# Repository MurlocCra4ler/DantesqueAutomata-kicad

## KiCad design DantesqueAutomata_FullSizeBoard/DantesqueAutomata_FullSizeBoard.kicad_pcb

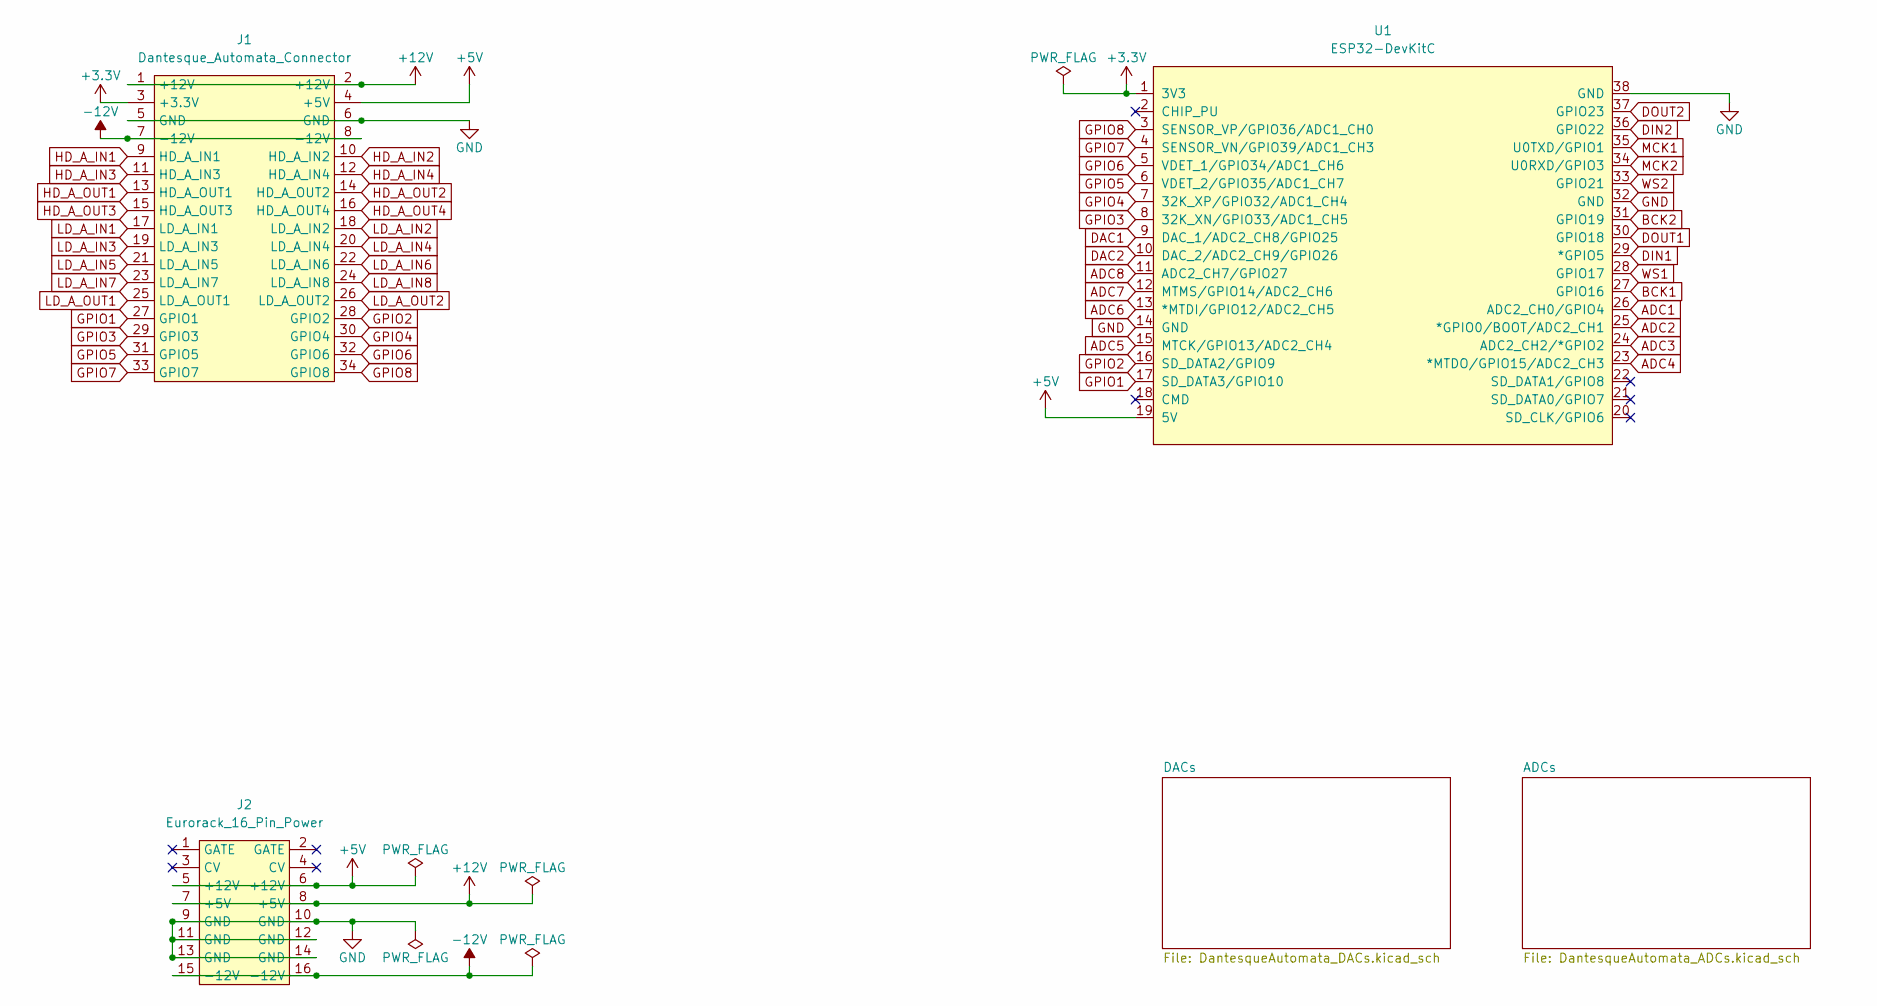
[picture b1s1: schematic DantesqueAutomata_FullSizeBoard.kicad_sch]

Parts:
J1: Dantesque_Automata_Connector
J2: Eurorack_16_Pin_Power
U1: ESP32-DevKitC

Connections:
+3.3V: J1.3 (+3.3V), U1.1 (3V3); also elsewhere on the board
+5V: J1.4 (+5V), J2.5 (+12V), J2.6 (+12V), U1.19 (5V); also elsewhere on the board
+12V: J1.1 (+12V), J1.2 (+12V), J2.7 (+5V), J2.8 (+5V); also elsewhere on the board
-12V: J1.7 (-12V), J1.8 (-12V), J2.15 (-12V), J2.16 (-12V); also elsewhere on the board
ADC1: U1.26 (ADC2_CH0/GPIO4); also elsewhere on the board
ADC2: U1.25 (*GPIO0/BOOT/ADC2_CH1); also elsewhere on the board
ADC3: U1.24 (ADC2_CH2/*GPIO2); also elsewhere on the board
ADC4: U1.23 (*MTDO/GPIO15/ADC2_CH3); also elsewhere on the board
ADC5: U1.15 (MTCK/GPIO13/ADC2_CH4); also elsewhere on the board
ADC6: U1.13 (*MTDI/GPIO12/ADC2_CH5); also elsewhere on the board
ADC7: U1.12 (MTMS/GPIO14/ADC2_CH6); also elsewhere on the board
ADC8: U1.11 (ADC2_CH7/GPIO27); also elsewhere on the board
BCK1: U1.27 (GPIO16); also elsewhere on the board
BCK2: U1.31 (GPIO19); also elsewhere on the board
DAC1: U1.9 (DAC_1/ADC2_CH8/GPIO25); also elsewhere on the board
DAC2: U1.10 (DAC_2/ADC2_CH9/GPIO26); also elsewhere on the board
DIN1: U1.29 (*GPIO5); also elsewhere on the board
DIN2: U1.36 (GPIO22); also elsewhere on the board
DOUT1: U1.30 (GPIO18); also elsewhere on the board
DOUT2: U1.37 (GPIO23); also elsewhere on the board
GND: J1.5 (GND), J1.6 (GND), J2.9 (GND), J2.10 (GND), J2.11 (GND), J2.12 (GND), J2.13 (GND), J2.14 (GND), U1.14 (GND), U1.32 (GND), U1.38 (GND); also elsewhere on the board
GPIO1: J1.27 (GPIO1), U1.17 (SD_DATA3/GPIO10)
GPIO2: J1.28 (GPIO2), U1.16 (SD_DATA2/GPIO9)
GPIO3: J1.29 (GPIO3), U1.8 (32K_XN/GPIO33/ADC1_CH5)
GPIO4: J1.30 (GPIO4), U1.7 (32K_XP/GPIO32/ADC1_CH4)
GPIO5: J1.31 (GPIO5), U1.6 (VDET_2/GPIO35/ADC1_CH7)
GPIO6: J1.32 (GPIO6), U1.5 (VDET_1/GPIO34/ADC1_CH6)
GPIO7: J1.33 (GPIO7), U1.4 (SENSOR_VN/GPIO39/ADC1_CH3)
GPIO8: J1.34 (GPIO8), U1.3 (SENSOR_VP/GPIO36/ADC1_CH0)
HD_A_IN1: J1.9 (HD_A_IN1); also elsewhere on the board
HD_A_IN2: J1.10 (HD_A_IN2); also elsewhere on the board
HD_A_IN3: J1.11 (HD_A_IN3); also elsewhere on the board
HD_A_IN4: J1.12 (HD_A_IN4); also elsewhere on the board
HD_A_OUT1: J1.13 (HD_A_OUT1); also elsewhere on the board
HD_A_OUT2: J1.14 (HD_A_OUT2); also elsewhere on the board
HD_A_OUT3: J1.15 (HD_A_OUT3); also elsewhere on the board
HD_A_OUT4: J1.16 (HD_A_OUT4); also elsewhere on the board
LD_A_IN1: J1.17 (LD_A_IN1); also elsewhere on the board
LD_A_IN2: J1.18 (LD_A_IN2); also elsewhere on the board
LD_A_IN3: J1.19 (LD_A_IN3); also elsewhere on the board
LD_A_IN4: J1.20 (LD_A_IN4); also elsewhere on the board
LD_A_IN5: J1.21 (LD_A_IN5); also elsewhere on the board
LD_A_IN6: J1.22 (LD_A_IN6); also elsewhere on the board
LD_A_IN7: J1.23 (LD_A_IN7); also elsewhere on the board
LD_A_IN8: J1.24 (LD_A_IN8); also elsewhere on the board
LD_A_OUT1: J1.25 (LD_A_OUT1); also elsewhere on the board
LD_A_OUT2: J1.26 (LD_A_OUT2); also elsewhere on the board
MCK1: U1.35 (U0TXD/GPIO1); also elsewhere on the board
MCK2: U1.34 (U0RXD/GPIO3); also elsewhere on the board
WS1: U1.28 (GPIO17); also elsewhere on the board
WS2: U1.33 (GPIO21); also elsewhere on the board

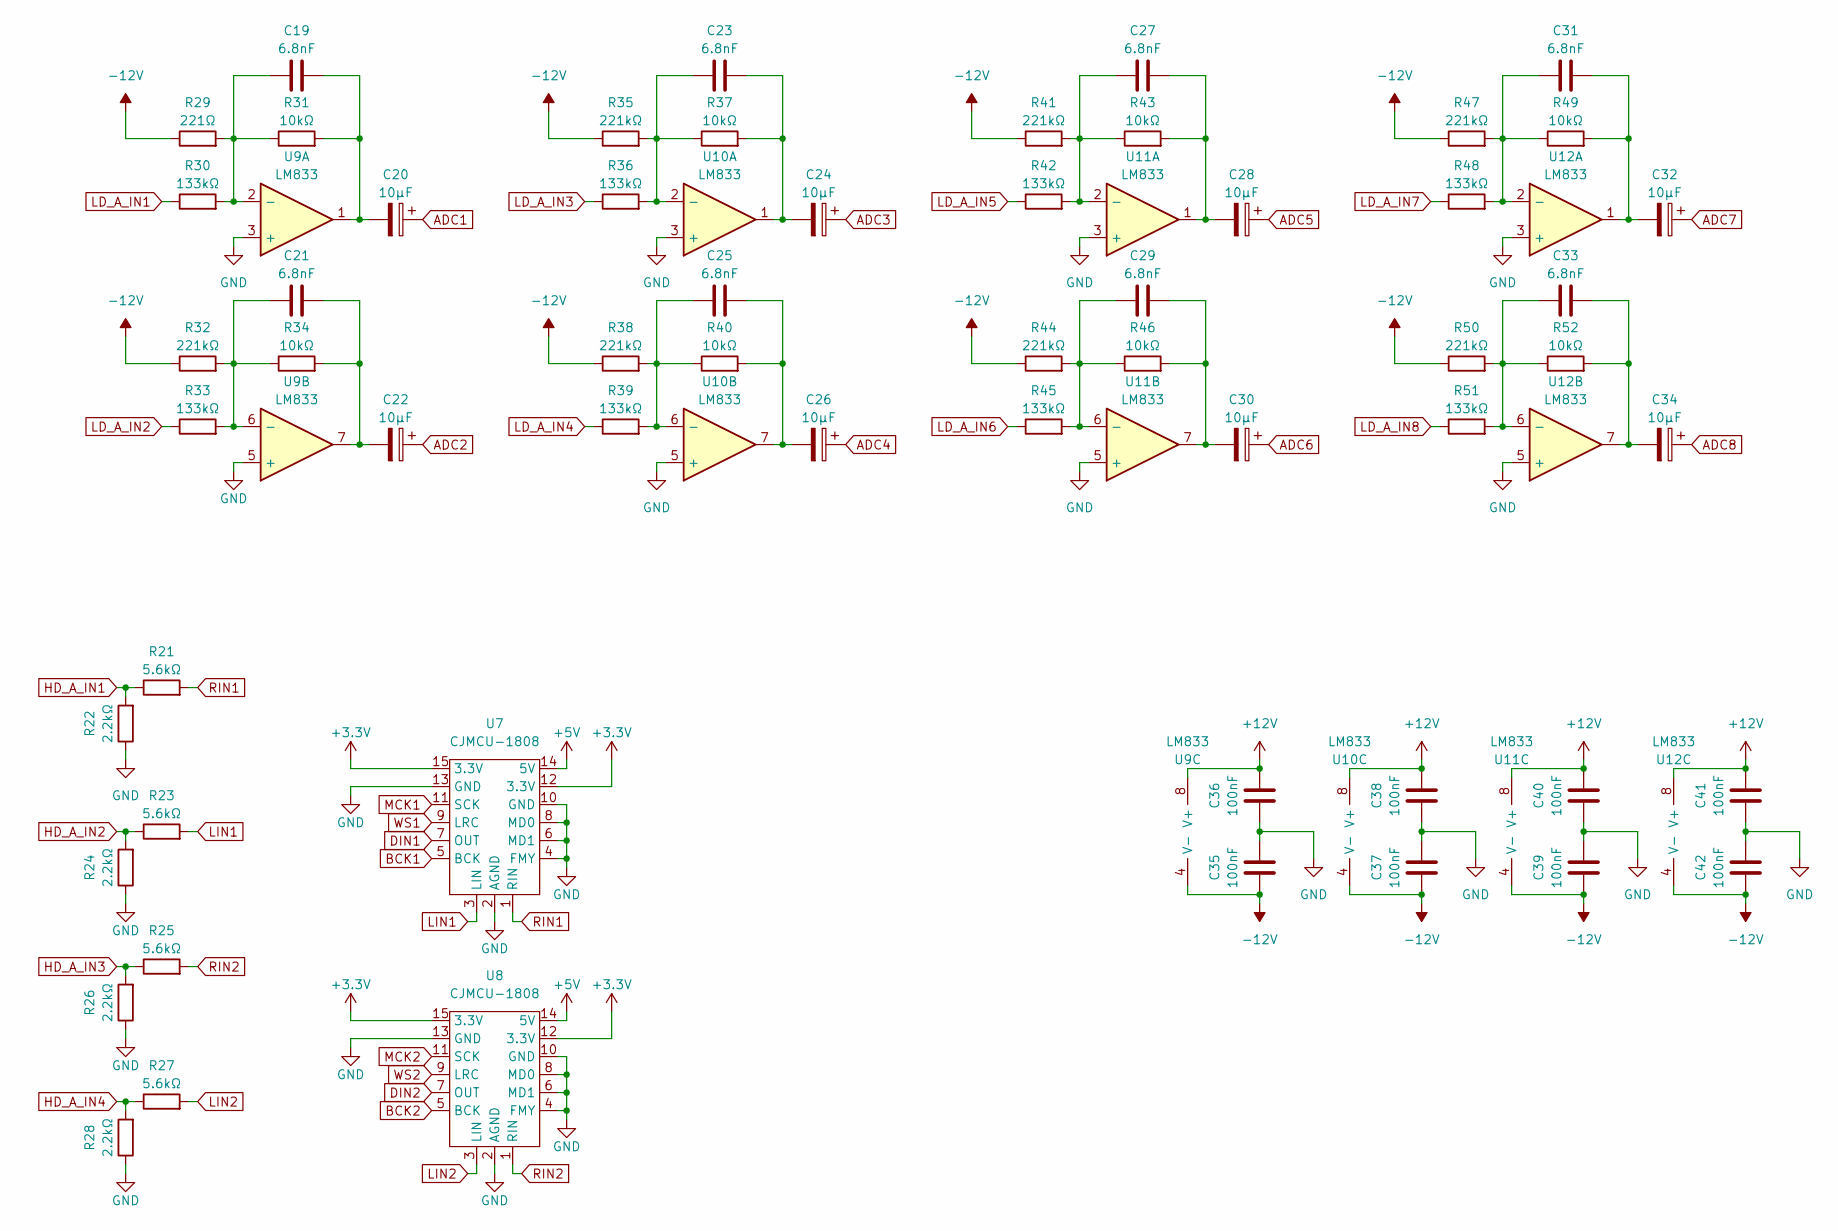
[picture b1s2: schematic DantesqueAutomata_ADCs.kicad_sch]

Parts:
C19, C21, C23, C25, C27, C29, C31, C33: 6.8nF; C_Disc_D4.3mm_W1.9mm_P5.00mm
C20, C22, C24, C26, C28, C30, C32, C34: 10µF; CP_Radial_D5.0mm_P2.00mm
C35, C36, C37, C38, C39, C40, C41, C42: 100nF; C_Disc_D4.3mm_W1.9mm_P5.00mm
R21, R23, R25, R27: 5.6kΩ; R_Axial_DIN0207_L6.3mm_D2.5mm_P10.16mm_Horizontal
R22, R24, R26, R28: 2.2kΩ; R_Axial_DIN0207_L6.3mm_D2.5mm_P10.16mm_Horizontal
R29: 221Ω; R_Axial_DIN0207_L6.3mm_D2.5mm_P10.16mm_Horizontal
R30, R33, R36, R39, R42, R45, R48, R51: 133kΩ; R_Axial_DIN0207_L6.3mm_D2.5mm_P10.16mm_Horizontal
R31, R34, R37, R40, R43, R46, R49, R52: 10kΩ; R_Axial_DIN0207_L6.3mm_D2.5mm_P10.16mm_Horizontal
R32, R35, R38, R41, R44, R47, R50: 221kΩ; R_Axial_DIN0207_L6.3mm_D2.5mm_P10.16mm_Horizontal
U7, U8: CJMCU-1808
U9, U10, U11, U12: LM833; DIP-8_W7.62mm

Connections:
+3.3V: U7.12 (3.3V), U7.15 (3.3V), U8.12 (3.3V), U8.15 (3.3V); also elsewhere on the board
+5V: U7.14 (5V), U8.14 (5V); also elsewhere on the board
+12V: C36.2, C38.2, C40.2, C41.2, U9.8 (V+), U10.8 (V+), U11.8 (V+), U12.8 (V+); also elsewhere on the board
-12V: C35.1, C37.1, C39.1, C42.1, R29.1, R32.1, R35.1, R38.1, R41.1, R44.1, R47.1, R50.1, U9.4 (V-), U10.4 (V-), U11.4 (V-), U12.4 (V-); also elsewhere on the board
ADC1: C20.1; also elsewhere on the board
ADC2: C22.1; also elsewhere on the board
ADC3: C24.1; also elsewhere on the board
ADC4: C26.1; also elsewhere on the board
ADC5: C28.1; also elsewhere on the board
ADC6: C30.1; also elsewhere on the board
ADC7: C32.1; also elsewhere on the board
ADC8: C34.1; also elsewhere on the board
BCK1: U7.5 (BCK); also elsewhere on the board
BCK2: U8.5 (BCK); also elsewhere on the board
DIN1: U7.7 (OUT); also elsewhere on the board
DIN2: U8.7 (OUT); also elsewhere on the board
GND: C35.2, C36.1, C37.2, C38.1, C39.2, C40.1, C41.1, C42.2, R22.1, R24.1, R26.1, R28.1, U7.2 (AGND), U7.4 (FMY), U7.6 (MD1), U7.8 (MD0), U7.10 (GND), U7.13 (GND), U8.2 (AGND), U8.4 (FMY), U8.6 (MD1), U8.8 (MD0), U8.10 (GND), U8.13 (GND), U9.3 (+), U9.5 (+), U10.3 (+), U10.5 (+), U11.3 (+), U11.5 (+), U12.3 (+), U12.5 (+); also elsewhere on the board
HD_A_IN1: R21.1, R22.2; also elsewhere on the board
HD_A_IN2: R23.1, R24.2; also elsewhere on the board
HD_A_IN3: R25.1, R26.2; also elsewhere on the board
HD_A_IN4: R27.1, R28.2; also elsewhere on the board
LD_A_IN1: R30.1; also elsewhere on the board
LD_A_IN2: R33.1; also elsewhere on the board
LD_A_IN3: R36.1; also elsewhere on the board
LD_A_IN4: R39.1; also elsewhere on the board
LD_A_IN5: R42.1; also elsewhere on the board
LD_A_IN6: R45.1; also elsewhere on the board
LD_A_IN7: R48.1; also elsewhere on the board
LD_A_IN8: R51.1; also elsewhere on the board
LIN1: R23.2, U7.3 (LIN)
LIN2: R27.2, U8.3 (LIN)
MCK1: U7.11 (SCK); also elsewhere on the board
MCK2: U8.11 (SCK); also elsewhere on the board
unnamed: C19.1, R29.2, R30.2, R31.1, U9.2 (-)
unnamed: C19.2, C20.2, R31.2, U9.1
unnamed: C21.1, R32.2, R33.2, R34.1, U9.6 (-)
unnamed: C21.2, C22.2, R34.2, U9.7
unnamed: C23.1, R35.2, R36.2, R37.1, U10.2 (-)
unnamed: C23.2, C24.2, R37.2, U10.1
unnamed: C25.1, R38.2, R39.2, R40.1, U10.6 (-)
unnamed: C25.2, C26.2, R40.2, U10.7
unnamed: C27.1, R41.2, R42.2, R43.1, U11.2 (-)
unnamed: C27.2, C28.2, R43.2, U11.1
unnamed: C29.1, R44.2, R45.2, R46.1, U11.6 (-)
unnamed: C29.2, C30.2, R46.2, U11.7
unnamed: C31.1, R47.2, R48.2, R49.1, U12.2 (-)
unnamed: C31.2, C32.2, R49.2, U12.1
unnamed: C33.1, R50.2, R51.2, R52.1, U12.6 (-)
unnamed: C33.2, C34.2, R52.2, U12.7
RIN1: R21.2, U7.1 (RIN)
RIN2: R25.2, U8.1 (RIN)
WS1: U7.9 (LRC); also elsewhere on the board
WS2: U8.9 (LRC); also elsewhere on the board

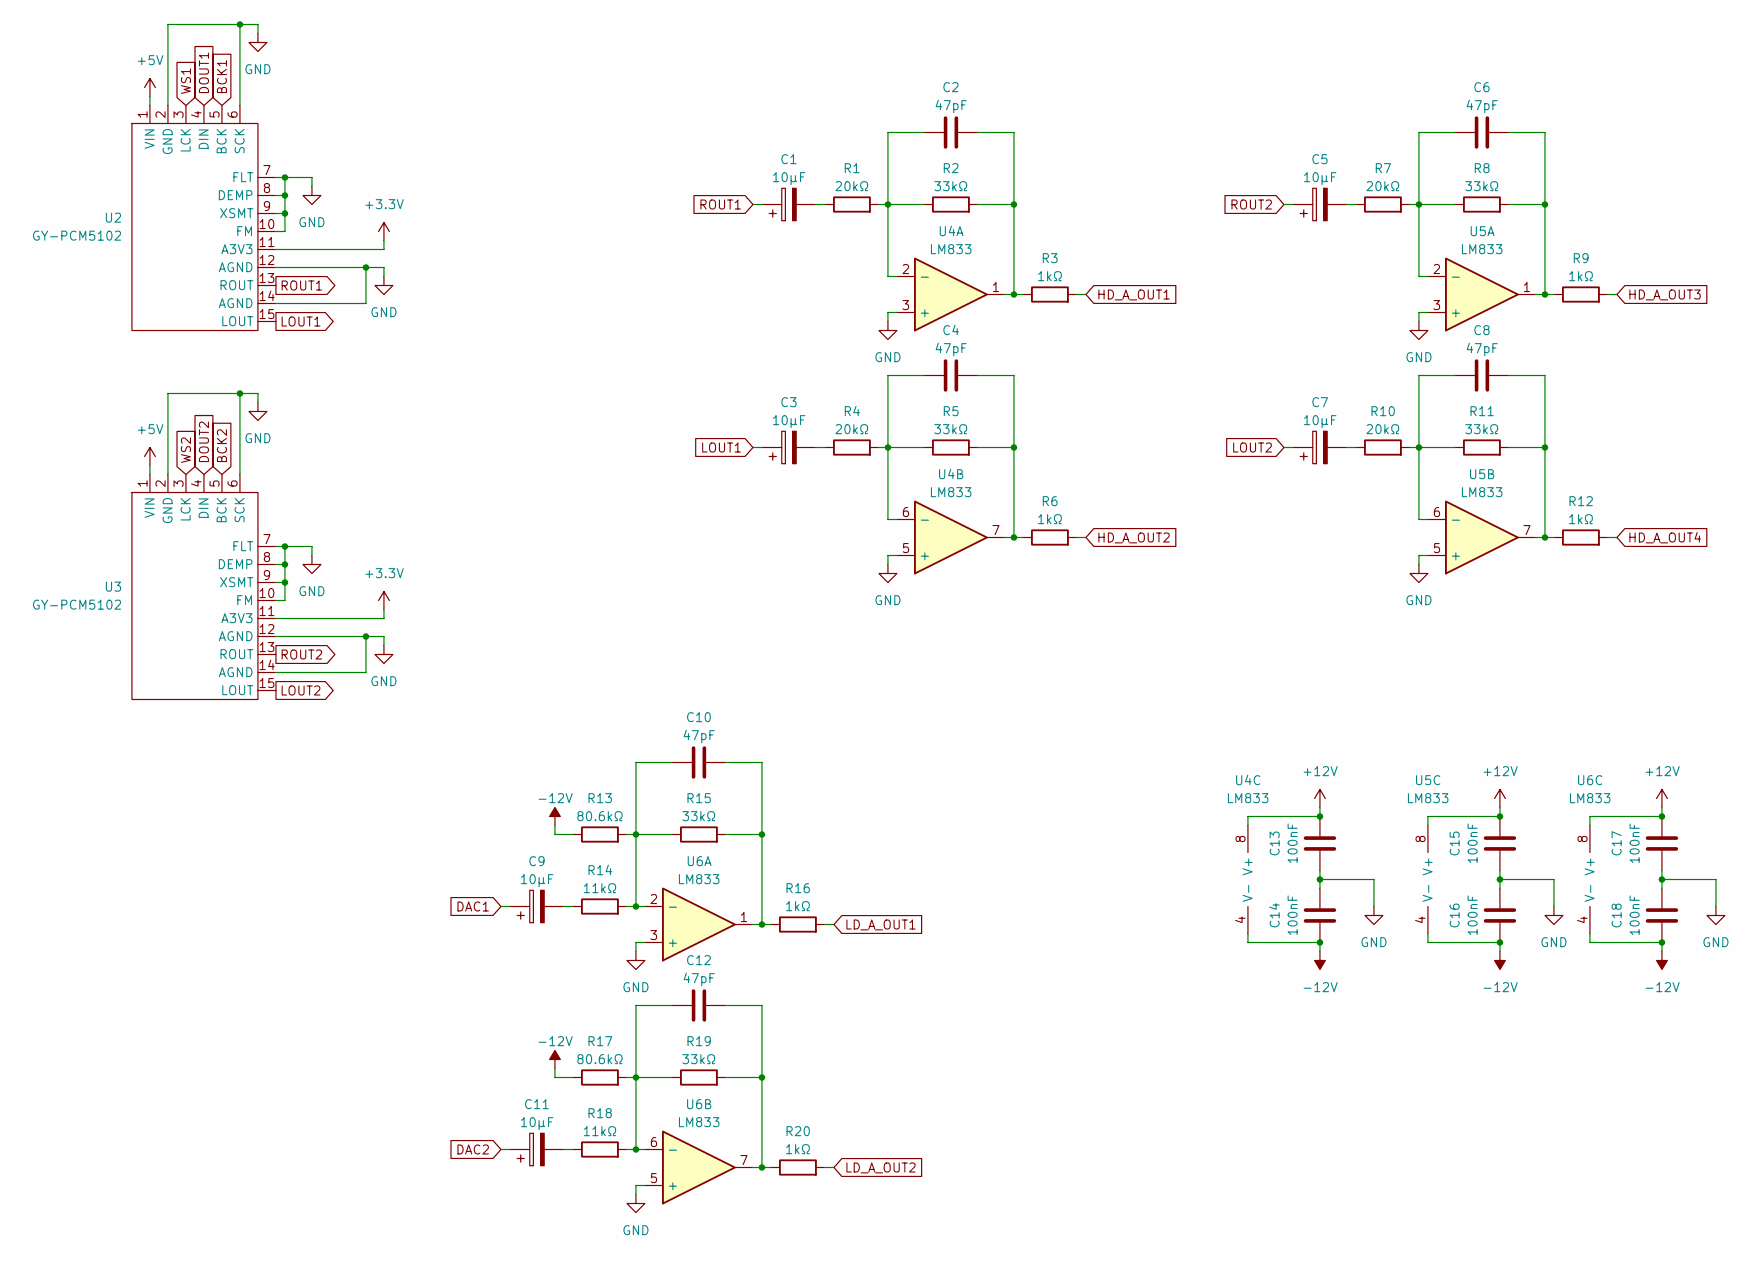
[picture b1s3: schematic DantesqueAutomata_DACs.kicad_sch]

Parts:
C1, C3, C5, C7, C9, C11: 10µF; CP_Radial_D5.0mm_P2.00mm
C2, C4, C6, C8, C10, C12: 47pF; C_Disc_D4.3mm_W1.9mm_P5.00mm
C13, C14, C15, C16, C17, C18: 100nF; C_Disc_D4.3mm_W1.9mm_P5.00mm
R1, R4, R7, R10: 20kΩ; R_Axial_DIN0207_L6.3mm_D2.5mm_P10.16mm_Horizontal
R2, R5, R8, R11, R15, R19: 33kΩ; R_Axial_DIN0207_L6.3mm_D2.5mm_P10.16mm_Horizontal
R3, R6, R9, R12, R16, R20: 1kΩ; R_Axial_DIN0207_L6.3mm_D2.5mm_P10.16mm_Horizontal
R13, R17: 80.6kΩ; R_Axial_DIN0207_L6.3mm_D2.5mm_P10.16mm_Horizontal
R14, R18: 11kΩ; R_Axial_DIN0207_L6.3mm_D2.5mm_P10.16mm_Horizontal
U2, U3: GY-PCM5102
U4, U5, U6: LM833; DIP-8_W7.62mm

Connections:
+3.3V: U2.11 (A3V3), U3.11 (A3V3); also elsewhere on the board
+5V: U2.1 (VIN), U3.1 (VIN); also elsewhere on the board
+12V: C13.2, C15.2, C17.2, U4.8 (V+), U5.8 (V+), U6.8 (V+); also elsewhere on the board
-12V: C14.1, C16.1, C18.1, R13.1, R17.1, U4.4 (V-), U5.4 (V-), U6.4 (V-); also elsewhere on the board
BCK1: U2.5 (BCK); also elsewhere on the board
BCK2: U3.5 (BCK); also elsewhere on the board
DAC1: C9.1; also elsewhere on the board
DAC2: C11.1; also elsewhere on the board
DOUT1: U2.4 (DIN); also elsewhere on the board
DOUT2: U3.4 (DIN); also elsewhere on the board
GND: C13.1, C14.2, C15.1, C16.2, C17.1, C18.2, U2.2 (GND), U2.6 (SCK), U2.7 (FLT), U2.8 (DEMP), U2.9 (XSMT), U2.10 (FM), U2.12 (AGND), U2.14 (AGND), U3.2 (GND), U3.6 (SCK), U3.7 (FLT), U3.8 (DEMP), U3.9 (XSMT), U3.10 (FM), U3.12 (AGND), U3.14 (AGND), U4.3 (+), U4.5 (+), U5.3 (+), U5.5 (+), U6.3 (+), U6.5 (+); also elsewhere on the board
HD_A_OUT1: R3.2; also elsewhere on the board
HD_A_OUT2: R6.2; also elsewhere on the board
HD_A_OUT3: R9.2; also elsewhere on the board
HD_A_OUT4: R12.2; also elsewhere on the board
LD_A_OUT1: R16.2; also elsewhere on the board
LD_A_OUT2: R20.2; also elsewhere on the board
LOUT1: C3.1, U2.15 (LOUT)
LOUT2: C7.1, U3.15 (LOUT)
unnamed: C1.2, R1.1
unnamed: C2.1, R1.2, R2.1, U4.2 (-)
unnamed: C2.2, R2.2, R3.1, U4.1
unnamed: C3.2, R4.1
unnamed: C4.1, R4.2, R5.1, U4.6 (-)
unnamed: C4.2, R5.2, R6.1, U4.7
unnamed: C5.2, R7.1
unnamed: C6.1, R7.2, R8.1, U5.2 (-)
unnamed: C6.2, R8.2, R9.1, U5.1
unnamed: C7.2, R10.1
unnamed: C8.1, R10.2, R11.1, U5.6 (-)
unnamed: C8.2, R11.2, R12.1, U5.7
unnamed: C9.2, R14.1
unnamed: C10.1, R13.2, R14.2, R15.1, U6.2 (-)
unnamed: C10.2, R15.2, R16.1, U6.1
unnamed: C11.2, R18.1
unnamed: C12.1, R17.2, R18.2, R19.1, U6.6 (-)
unnamed: C12.2, R19.2, R20.1, U6.7
ROUT1: C1.1, U2.13 (ROUT)
ROUT2: C5.1, U3.13 (ROUT)
WS1: U2.3 (LCK); also elsewhere on the board
WS2: U3.3 (LCK); also elsewhere on the board

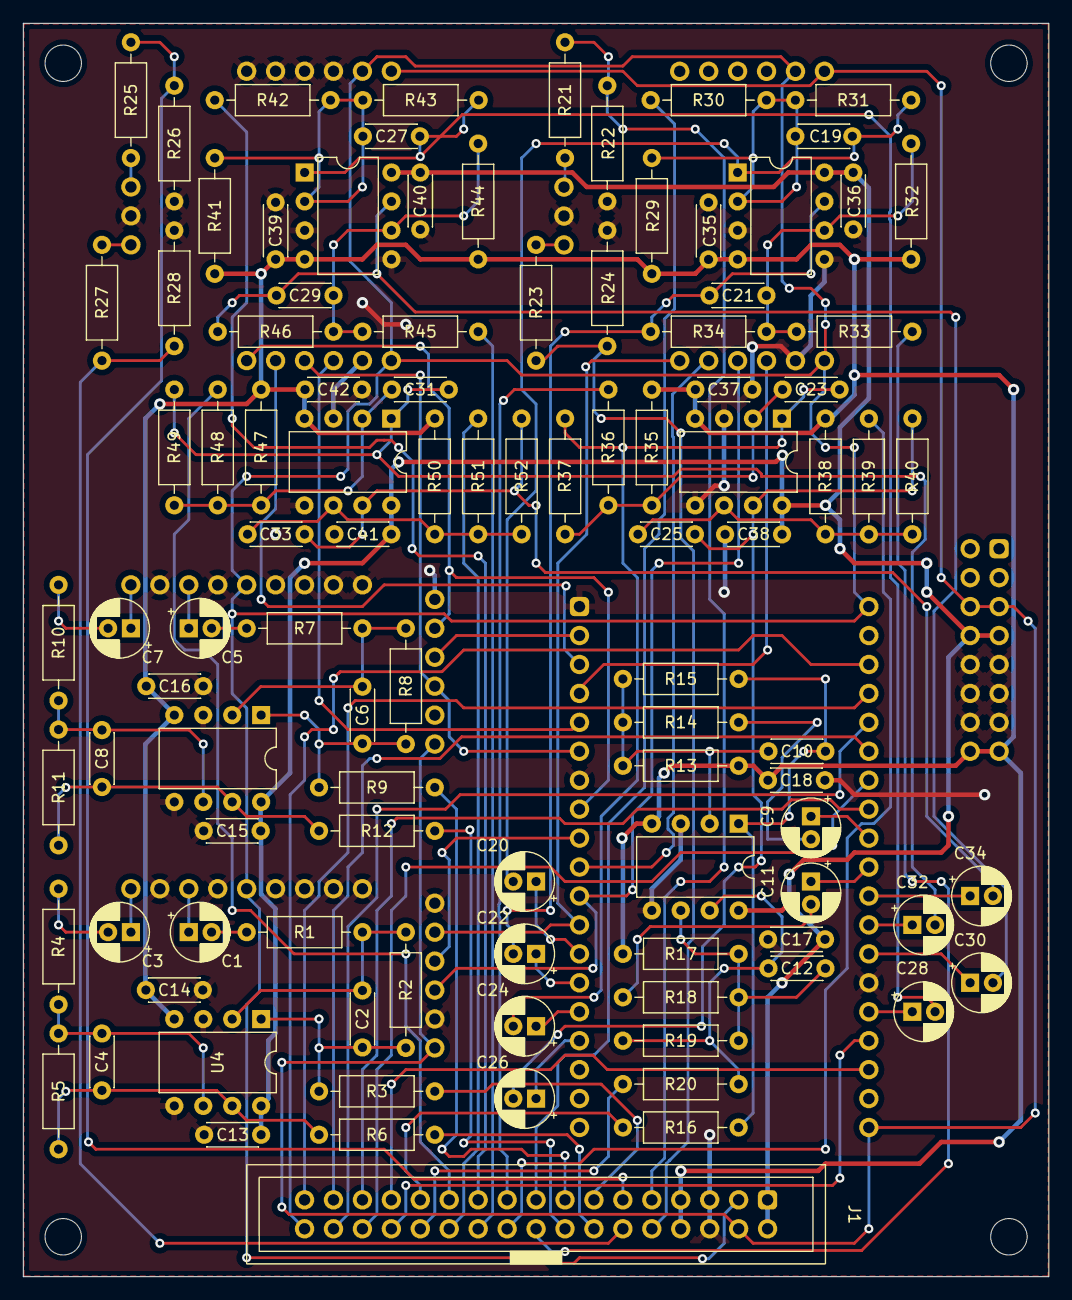
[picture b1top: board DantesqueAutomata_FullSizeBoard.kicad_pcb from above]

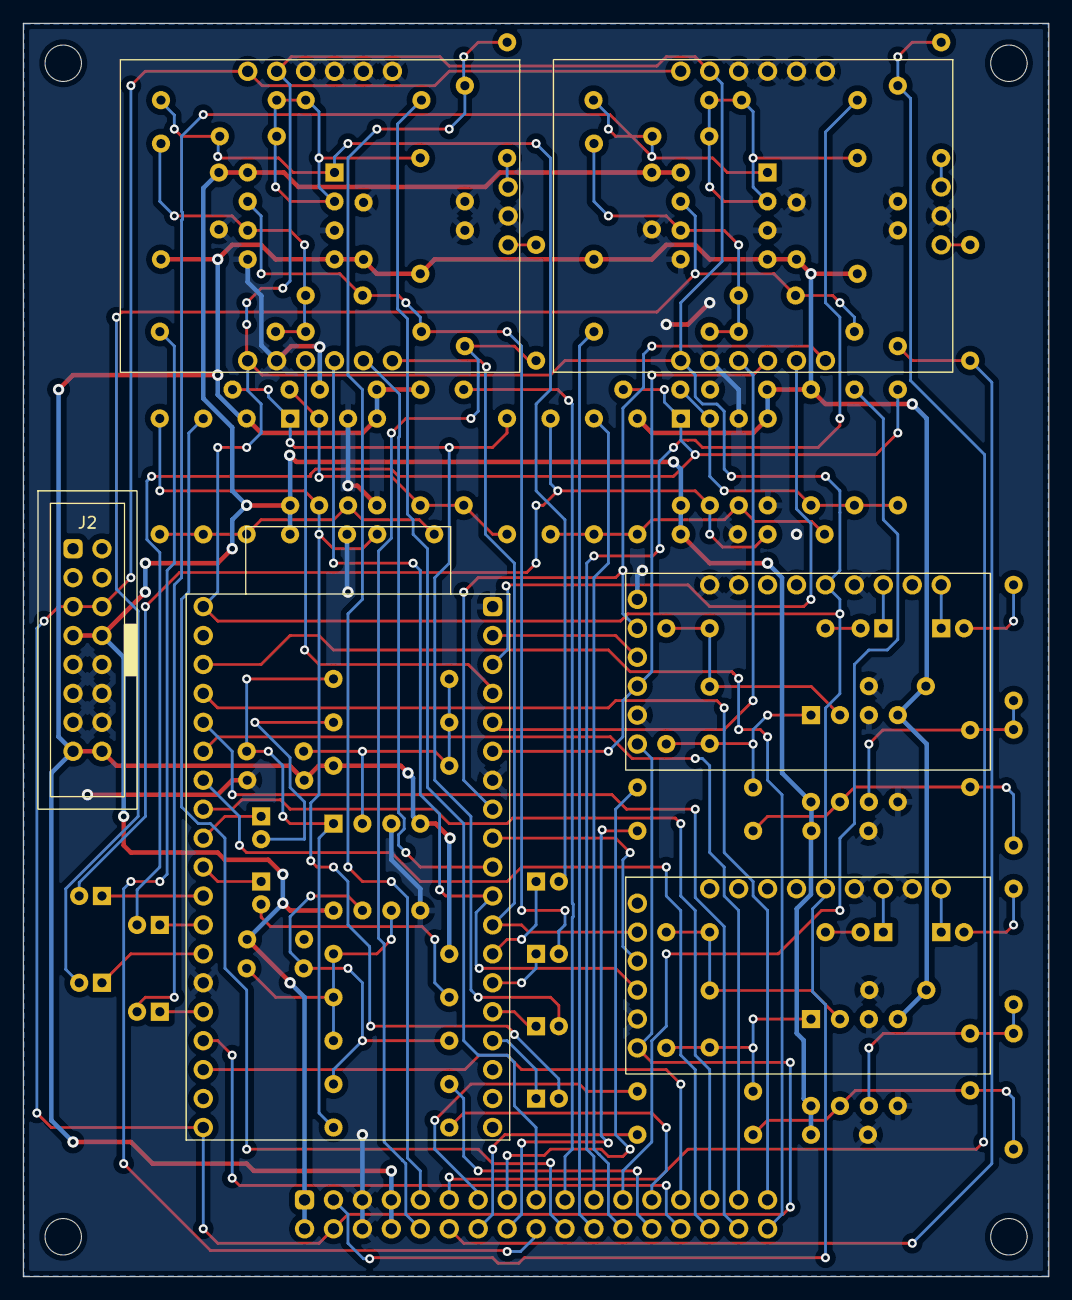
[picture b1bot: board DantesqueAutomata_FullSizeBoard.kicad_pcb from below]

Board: 2 copper layers, 90.0 x 110.0 mm, 108 parts (6 on the bottom side), 93 nets.

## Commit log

2022-07-05 Added the CJMCU-1808 audio module
2022-07-08 First draft for full size board
2022-07-11 FullSizeBoard Revision 1 finished
2022-07-12 added symbol/footprint library for connectors
2022-07-13 improved pcb design of full size board
2022-07-13 fixed mounting holes
2022-07-14 increased drill hole size for board and footprints
